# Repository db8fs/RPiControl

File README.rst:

##########
RPiControl
##########

***************************
RaspberryPi 3 Interface
***************************

Hardware
==============

Prozessor
^^^^^^^^^

Der RaspberryPi3 ist ein Ein-Platinen-Computer auf der Grundlage der ARM-Prozessorarchitektur, welche durch die Firma Broadcom lizensiert und im SoC (https://www.raspberrypi.org/wp-content/uploads/2012/02/BCM2835-ARM-Peripherals.pdf) implementiert wurde. Es handelt sich dabei um eine **Quad-Core-SMP**-Architektur mit einem Basistakt von **1.2Ghz** und einer Adressbreite von **64-Bit**. 

GPU
^^^
Der BCM2835-Prozessor ist als System-On-Chip konzipiert und stellt einen Grafikprozessor auf der Grundlage der Broadcom-VideoCoreIV-IP (http://elinux.org/Raspberry_Pi_VideoCore_APIs) bereit. Diese ist in der Lage, Full-HD-Videos abzuspielen und stellt auch OpenGL ES 2.0 bzw. OpenVG für Anwendungen bereit.

Speicher
^^^^^^^^
Wie für fast jegliche Art von Computersystem ist auch für den RaspberryPi3 eine **Speicherhierarchie** definiert. Der schnelle, aber flüchtige Arbeitsspeicher (**RAM**) des RaspberryPi ist mit 900Mhz getaktet (LPDDR2) und steht in einer Kapazität von **1GB** bereit. Das langsame, aber persistente Halten von Daten wird durch eine externe SD-Karte realisiert. 

Netzwerk
^^^^^^^^

Ein wesentlicher Unterschied neben der erhöhten Performance gegenüber dem RaspberryPi2 ist eine neu hinzugekommene Wireless-Funktionalität. So ist der RPi3 bereits im Auslieferungszustand in der Lage, **Bluetooth-LowEnergy** und WLAN-Verbindungen (IEEE 802.11n) herzustellen. Diese Funktionalität wird über den Chipsatz BCM43143 (http://www.cypress.com/file/298756/download) realisiert. Zusätzlich steht wie in den Vorgängermodellen des RPi eine RJ45-Schnittstelle bereit, über die 100MBit-Ethernetverbindungen hergestellt werden können. 

Peripherie
^^^^^^^^^^

Zusätzliche Komponenten des RaspberryPi3 sind die erweiterte Anzahl von USB-Schnittstellen (4x USB 2.0) gegenüber den 2xUSB1.1 vom ursprünglichen Board aus dem Jahre 2012), welche über das Bauteil SMSC LAN9514 (http://ww1.microchip.com/downloads/en/DeviceDoc/9514.pdf) realisiert wird (dieses implementiert gleichzeitig auch den Ethernet-Stack). 
Daneben ist für den RPi3 auch eine **CSI-Kameraschnittstelle** für serielle Datenübertragung von HD-Kameramodulen vorgesehen, mit der entsprechende Kameramodule hochauflösend an den BCM-Prozessor angebunden werden können. 

Zur Darstellung der Benutzeroberfläche dient eine **HDMI-** und eine **DSI-Displayschnittstelle**, über die mittels Differenzsignalen hochfrequent und störungsfrei Daten zu Displays übertragen werden können (**LVDS**). Dies entspricht im Wesentlichen dem Verhalten der HDMI-Schnittstelle, welche zum Anschluss externer Monitore bereitsteht und deren LVDS-Signale durch die oben genannte VideoCore-GPU generiert werden. 

Zur Ausgabe akustischer Signale (Soundkarte) steht ein kombinierter A/V-Adapter zur Verfügung, der durch eine 3.5mm Klinkenstecker eine Stereoausgabe ermöglicht. Zusätzlich wird über einen dritten Kanal ein Composite-Videosignal (PAL/NTSC) bereitgestellt, was zur Videoausgabe auf nicht-HDMI-kompatibler Hardware verwendet werden kann. 

Erweiterungen
^^^^^^^^^^^^^
Für das hier dokumentierte Projekt ist allerdings eine andere Eigenschaft des RaspberryPi entscheidend: der RaspberryPi 3 besitzt nämlich eine 40-polige Steckerleiste zur Anbindung
externer Peripherie. Darüber können universell benutzbare Ein-/Ausgabe-Pins (GPIO=General Purpose I/O) mit LVTTL Pegeln (**3.3V**) geschaltet bzw. hochohmig gelesen werden. Manche
dieser GPIO Pins besitzen eine Doppelbelegung, die bei Konfiguration der richtigen Register des BroadCom-SoCs die Zweitfunktionalität freischaltet. Dies betrifft z.B. Platinenbusse wie **SPI** oder **I²C**, die Ansteuerung von RS232-/ oder RS485-Treibern (**UART**), aber auch die Generierung von externen Signalformen mittels Hardware-unterstützter Pulsweitenmodulation (**PWM**).
Maximal belastbar sind die GPIO-Ausgabekanäle mit **50mA**, was zum direkten Schalten von LEDs ausreicht, für größere Lasten aber Bipolar- bzw. Feldeffekttransistoren benötigt.

Betriebssystem
^^^^^^^^^^^^^^

Der RaspberryPi kann mit verschiedenen Betriebssystemen betrieben werden. Unter anderem stehen verschiedene Linux-Distributionen wie Raspbian (http://www.raspbian.org) oder das für MediaCenter optimierte (http://www.openelec.tv) zur Verfügung. Auch eine Verwendung mit Microsoft-Plattformen ist möglich, so kann etwa auch Windows10-IoT (https://developer.microsoft.com/de-de/windows/iot) für den RaspberryPi3 verwendet werden.

Programmierung
^^^^^^^^^^^^^^

Zur Programmierung eigener Anwendungen ist für Linux-Betriebssysteme die Programmiersprache **Python** (http://www.python.org) das Mittel der Wahl. Sie stellt eine sehr einfache und für Einsteiger leicht zu erlernende Syntax bereit und kann durch **PyQt** (https://riverbankcomputing.com/software/pyqt/intro) leicht grafische Anwendungen erzeugen. Zur Ansteuerung der GPIOs kann die Softwarekomponente **WiringPi** (http://raspberrypiguide.de/howtos/raspberry-pi-gpio-how-to/) genutzt werden. Neben Python stehen auch Compiler für Programmiersprachen wie C/C++, Java oder ADA (http://www.adacore.com/press/adacore-introduces-gnat-gpl-2015-for-the-raspberry-pi-2) bereit. 

Für die Verwendung von Windows 10 IoT muss statt dessen das VisualStudio 2015 (https://developer.microsoft.com/en-us/windows/iot/docs/setuppcrpi) verwendet werden. Damit wird eine Programmierung mit **C#** und dem **.NET Framework** möglich.

GPIO-Extender
^^^^^^^^^^^^^

Hauptkomponente des Projekts ist der integrierte Schaltkreis MCP23017 (http://cdn-reichelt.de/documents/datenblatt/A200/DS_MCP23017.pdf), der als GPIO-Extender fungiert und über den I²C-Bus vom RaspberryPi aus gesteuert werden kann.

Die wesentliche Aufgabe des Bausteins ist die Behebung der Limitierung von I/O-Ports. Der RaspberryPi kann als I²C-Master theoretisch bis zu 127 Slaves adressieren, die Einschränkung soll hier bei maximal 8 Teilnehmern liegen.&lt;p&gt; Der MCP23017 unterstützt zwei Kanäle mit je einer Breite von 8-Bit. Durch Konfiguration eines Datenrichtungsregisters können deren Pins zwischen Input- und Output umgeschaltet werden.

Expansion-Header
^^^^^^^^^^^^^^^^
Die Expansion-Header entsprechen Stiftleisten zur Erweiterung der Funktionalität. So können für ein bestimmte Einsatzzweck erstellte Lochraster- bzw. Platinenaufbauten mit dem Board verwendet werden, solange sie den gleichen Footprint verwenden und die elektrischen Gegebenheiten passend antizipieren.

RJ-45-Steckverbinder
^^^^^^^^^^^^^^^^^^^^^
Zur Verbindung von Busteilnehmern kommen RJ-45-Steckverbinder zum Einsatz, die in der Netzwerktechnik weit verbreitet sind und daher leicht verfügbar bzw. erweiterbar sind. Das betrifft hauptsächlich die einfache und wartungsfreie Montage von Slave-Modulen im Gesamtsystem des Aufbaus. 

**Keine Kompatibilität zu Ethernet-Switches/-Hubs**!

Die Belegung  der RJ-45-Buchse ist **proprietär und inkompatibel zu Ethernet**. 

Konkret leisten muss die RJ45-Buchse:

- Masseverbindung
- Reserviert
- I²C-Clock (+3.3V LVTTL)
- I²C-Data (+3.3V LVTTL)
- +12V DC-Versorgungsspannung
- Reset (Low-Active, +3.3V LVTTL)
- Reserviert
- Reserviert

Somit wird sichergestellt, dass selbst bei Verklemmung des I²C-Busses, ein durch den I²C-Master gesteuertes Reset ausgelöst werden kann. Die restlichen Aufgaben sind Datentransport und Bereitstellung einer gemeinsamen Spannungsquelle für alle Slaves. Die handelsüblichen Cat5-Kabel bieten für dieses kleine I²C-Bussystem auch den Vorteil einer recht hohen Abschirmung gegenüber HF-Einströmungen, da die Adern paarweise geschirmt sind (Twisted-Pair). Damit sollte eine für PWM ausreichend hohe Taktung des I²C-Busses auch über mal 2-3m
hin gewährleistet sein.

I²C-Bus
^^^^^^^
Zur Kommunikation zwischen RaspberryPi und den angeschlossenen Verbrauchern dient der von Philips entwickelte I²C-Bus, der ähnlich wie der SPI-Bus zur Kommunikation zwischen IC auf und zwischen Leiterplatten dient (**I²C=Inter-Integrated-Circuits**). Aus diesem Design folgen ein paar ernsthafte Limitierungen:

- Der I²C-Bus ist **nicht differentiell**, d.h. es wird **nicht** wie etwa bei CAN- oder RS485 mit zwei Datenpotentialen (D+, D-) gearbeitet, deren Differenzspannung vom Empfänger gebildet wird.
- I²C ist somit anfällig für Gleichtaktstörungen (z.B. Zündfunken), hat aufgrund der niedrigen (LV)TTL-Pegel eine begrenzte Reichweite und benötigt ähnlich wie die RS232 immer eine gemeinsame Masse als Bezugspotential.
- I²C ist ein **getakteter Bus**
- I²C ist ein Master-Slave-Bussystem 
- Anzahl Teilnehmer ist auf 127 begrenzt
- Datenbreite für Register ist im Durchschnitt bei 16-Bit (implementierungabhängig)
- Terminierung erforderlich
- Datenraten von bis zu 5Mbit/s möglich
- serieller Bus (MSB-first Übertragung)

Diese Master-Slave-Busarchitektur ermöglicht es dem Master, zyklisch Werte vom Bus abzufragen
(**Polling**). Manche IC-Implementierungen ermöglichen zusätzlich die Verwendung von externen Interrupt-Pins, welche OnChange-Ereignisse signalisieren können. Aufgrund der dadurch resultierenden Verdrahtungskomplexität bietet sich das allerdings nur in speziellen Anwendungsfällen an, wo z.B. ein preiswerter und leistungsbegrenzter 8-Bit-Mikrocontroller (möglicherweise mit Optimierung auf maximale Batterielaufzeit) aufgrund eigener Resourcenrestriktionen und anderen integrierten Funktionen nicht ständig auf den I²C-Bus pollen kann.

Aus der Perspektive des RaspberryPi als I²C-Master bietet sich I²C sehr an, da mit den **i2c-tools** und dem Linux-Kernel-Modul **i2c-bcm2708** eine sehr leistungsstarke und komfortable Schnittstelle zur Arbeit mit I²C bereit steht. Die sehr gute Linux-Unterstützung für I²C rührt u.a. historisch auch daher, dass viele Temperatur-Sensoren auf PC-Mainboards über dieses Protokoll adressiert wurden (Stichwort **lm-sensors**).

Die I²C-Slaves als Teilnehmer müssen mit **eindeutigen Adressen** kodiert sein. Zu diesem Zweck dienen beim MCP23017 die Pins A[0..2], wodurch sich 2³=8 Teilnehmer unterscheiden lassen. Die Slave-Adressierung wird durch den montierten DIP-Schalter durchgeführt.

Versorgung
^^^^^^^^^^
Die Spannungsversorgung ist einheitlich auf +12V DC sichergestellt. Dies zum Einen dem Leistungsteil geschuldet, dessen Verbraucher diese Spannung erfordern, zum Anderen bietet sich dieser Spannungslevel aufgrund der Versorgung durch Kfz-Netzteile etc. an. 
Eine wichtige Rolle für die Versorgungsspannung spielt der I²C-Bus, der zur Kommunikation zwischen dem RaspberryPi und den Busteilnehmern dient. I²C funktioniert im Gegensatz zu CAN-
Bus oder anderen Feldbussystemen wie RS-485 **nicht differenziell**. Das bedeutet in der Konsequenz, dass sowohl **eine gemeinsame Masse**, als auch **ein gemeinsames Versorgungpotential** notwendig ist.

Der Broadcom-ARM-Prozessor des RaspberryPi verwendet sowohl für GPIOs, als auch für SPI und I²C-Bus ein LVTTL-Pegel, d.h. +3.3V, welche sowohl für den I²C-Takt, als auch
für die I²C-Datenleitung gelten.

Somit ergibt sich in der Konsequenz, dass als kleinster gemeinsamer Nenner zwischen RaspberryPi und GPIO-Extender beide auf LVTTL betrieben werden sollten.

Für diese Zwecke wird ein Low-Drop-Spannungsregler von Texas Instruments vom Typ **LM1117** (http://www.ti.com/lit/ds/symlink/lm1117.pdf) eingesetzt.

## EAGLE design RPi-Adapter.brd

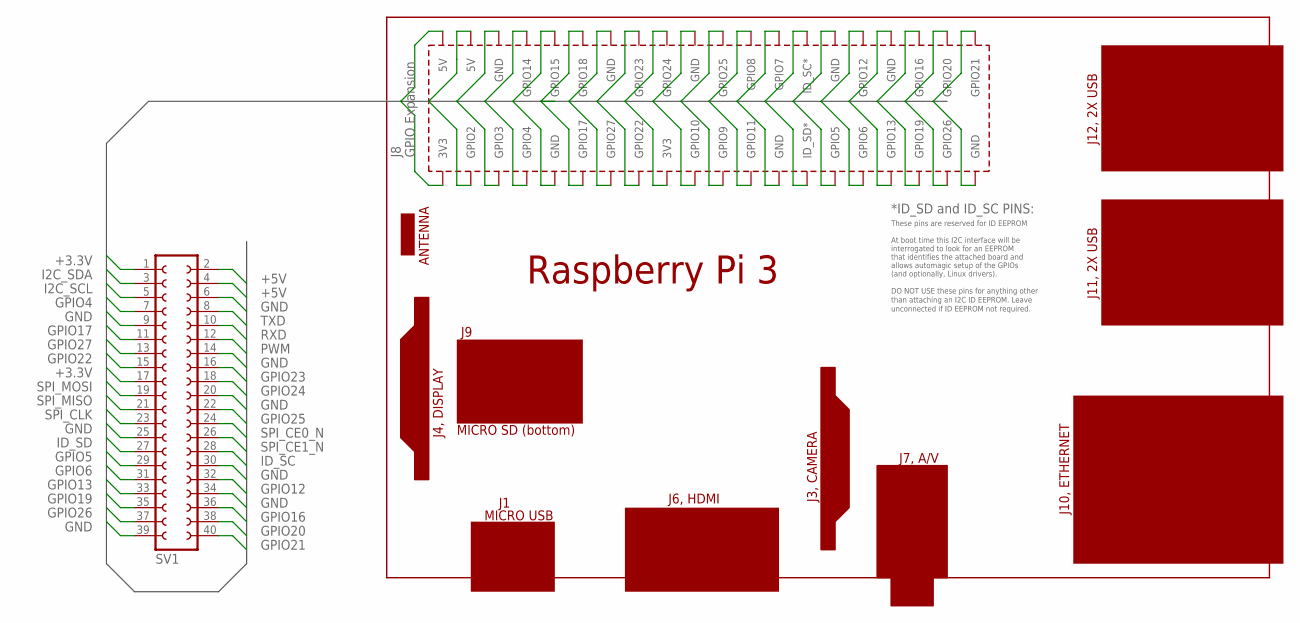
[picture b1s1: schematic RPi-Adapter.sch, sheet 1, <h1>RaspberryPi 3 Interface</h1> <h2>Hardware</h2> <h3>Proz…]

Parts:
SV1: FE20-2

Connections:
+3.3V: SV1.1, SV1.17; also elsewhere on the board
+5V: SV1.2, SV1.4; also elsewhere on the board
GND: SV1.6, SV1.9, SV1.14, SV1.20, SV1.25, SV1.30, SV1.34, SV1.39; also elsewhere on the board
GPIO4: SV1.7; also elsewhere on the board
GPIO5: SV1.29
GPIO6: SV1.31
GPIO12: SV1.32
GPIO13: SV1.33
GPIO16: SV1.36
GPIO17: SV1.11
GPIO19: SV1.35
GPIO20: SV1.38
GPIO21: SV1.40
GPIO22: SV1.15
GPIO23: SV1.16
GPIO24: SV1.18
GPIO25: SV1.22
GPIO26: SV1.37
GPIO27: SV1.13
I2C_SCL: SV1.5; also elsewhere on the board
I2C_SDA: SV1.3; also elsewhere on the board
ID_SC: SV1.28
ID_SD: SV1.27
PWM: SV1.12; also elsewhere on the board
RXD: SV1.10; also elsewhere on the board
SPI_CE0_N: SV1.24; also elsewhere on the board
SPI_CE1_N: SV1.26; also elsewhere on the board
SPI_CLK: SV1.23; also elsewhere on the board
SPI_MISO: SV1.21; also elsewhere on the board
SPI_MOSI: SV1.19; also elsewhere on the board
TXD: SV1.8; also elsewhere on the board

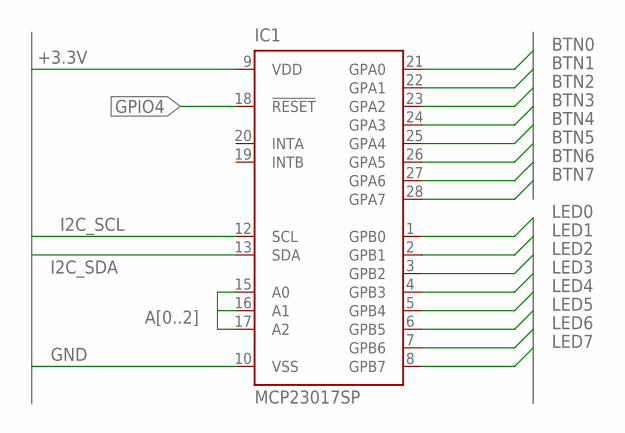
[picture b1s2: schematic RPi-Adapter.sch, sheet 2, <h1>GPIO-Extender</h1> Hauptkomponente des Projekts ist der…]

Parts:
IC1: MCP23017SP; DIL28-3

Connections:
+3.3V: IC1.9 (VDD); also elsewhere on the board
A0: IC1.15 (A0); also elsewhere on the board
A1: IC1.16 (A1); also elsewhere on the board
A2: IC1.17 (A2); also elsewhere on the board
BTN0: IC1.21 (GPA0); also elsewhere on the board
BTN1: IC1.22 (GPA1); also elsewhere on the board
BTN2: IC1.23 (GPA2); also elsewhere on the board
BTN3: IC1.24 (GPA3); also elsewhere on the board
BTN4: IC1.25 (GPA4); also elsewhere on the board
BTN5: IC1.26 (GPA5); also elsewhere on the board
BTN6: IC1.27 (GPA6); also elsewhere on the board
BTN7: IC1.28 (GPA7); also elsewhere on the board
GND: IC1.10 (VSS); also elsewhere on the board
GPIO4: IC1.18 (!RESET); also elsewhere on the board
I2C_SCL: IC1.12 (SCL); also elsewhere on the board
I2C_SDA: IC1.13 (SDA); also elsewhere on the board
LED0: IC1.1 (GPB0); also elsewhere on the board
LED1: IC1.2 (GPB1); also elsewhere on the board
LED2: IC1.3 (GPB2); also elsewhere on the board
LED3: IC1.4 (GPB3); also elsewhere on the board
LED4: IC1.5 (GPB4); also elsewhere on the board
LED5: IC1.6 (GPB5); also elsewhere on the board
LED6: IC1.7 (GPB6); also elsewhere on the board
LED7: IC1.8 (GPB7); also elsewhere on the board

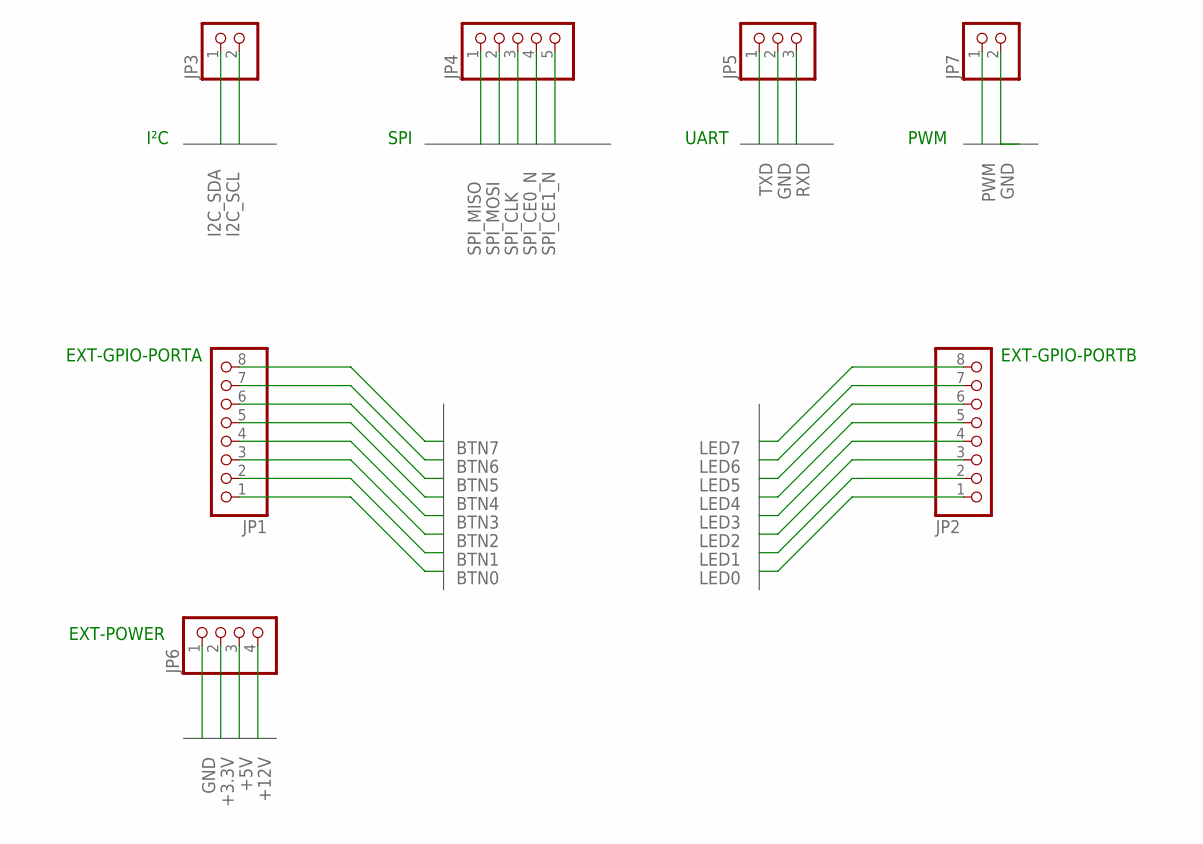
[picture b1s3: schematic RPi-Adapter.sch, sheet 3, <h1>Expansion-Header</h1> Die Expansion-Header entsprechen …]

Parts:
JP1, JP2: PINHD-1X8; 1X08
JP3, JP7: PINHD-1X2; 1X02
JP4: PINHD-1X5; 1X05
JP5: PINHD-1X3; 1X03
JP6: PINHD-1X4; 1X04

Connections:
+3.3V: JP6.2; also elsewhere on the board
+5V: JP6.3; also elsewhere on the board
+12V: JP6.4; also elsewhere on the board
BTN0: JP1.1; also elsewhere on the board
BTN1: JP1.2; also elsewhere on the board
BTN2: JP1.3; also elsewhere on the board
BTN3: JP1.4; also elsewhere on the board
BTN4: JP1.5; also elsewhere on the board
BTN5: JP1.6; also elsewhere on the board
BTN6: JP1.7; also elsewhere on the board
BTN7: JP1.8; also elsewhere on the board
GND: JP5.2, JP6.1, JP7.2; also elsewhere on the board
I2C_SCL: JP3.2; also elsewhere on the board
I2C_SDA: JP3.1; also elsewhere on the board
LED0: JP2.1; also elsewhere on the board
LED1: JP2.2; also elsewhere on the board
LED2: JP2.3; also elsewhere on the board
LED3: JP2.4; also elsewhere on the board
LED4: JP2.5; also elsewhere on the board
LED5: JP2.6; also elsewhere on the board
LED6: JP2.7; also elsewhere on the board
LED7: JP2.8; also elsewhere on the board
PWM: JP7.1; also elsewhere on the board
RXD: JP5.3; also elsewhere on the board
SPI_CE0_N: JP4.4; also elsewhere on the board
SPI_CE1_N: JP4.5; also elsewhere on the board
SPI_CLK: JP4.3; also elsewhere on the board
SPI_MISO: JP4.1; also elsewhere on the board
SPI_MOSI: JP4.2; also elsewhere on the board
TXD: JP5.1; also elsewhere on the board

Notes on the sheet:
EXT-GPIO-PORTA
EXT-GPIO-PORTB
I²C
SPI
UART
EXT-POWER
PWM

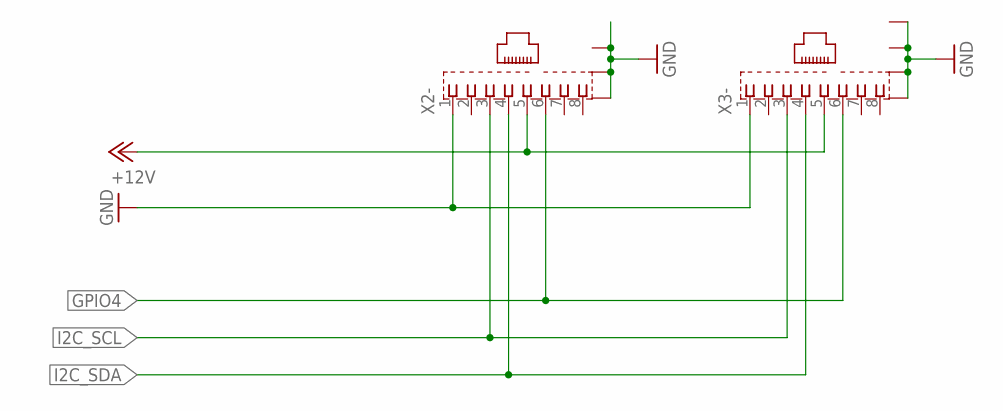
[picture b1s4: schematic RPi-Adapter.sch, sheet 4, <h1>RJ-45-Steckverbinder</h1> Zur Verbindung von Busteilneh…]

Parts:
X2, X3: RJ45

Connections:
+12V: X2.5, X3.5; also elsewhere on the board
GND: X2.1, X2.G1 (1), X2.G2 (1), X2.G3 (1), X3.1, X3.G1 (1), X3.G2 (1), X3.G3 (1), X3.G4 (1); also elsewhere on the board
GPIO4: X2.6, X3.6; also elsewhere on the board
I2C_SCL: X2.3, X3.3; also elsewhere on the board
I2C_SDA: X2.4, X3.4; also elsewhere on the board

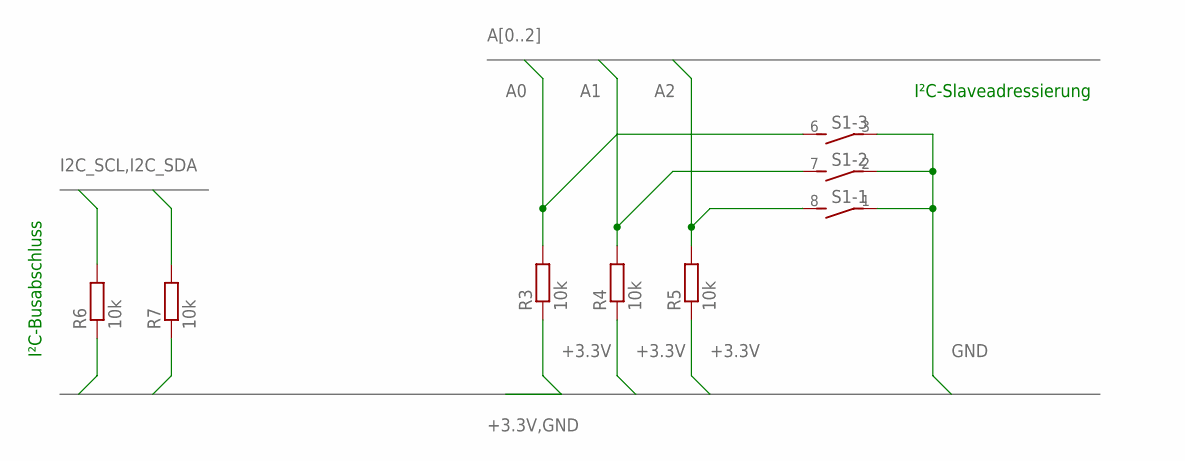
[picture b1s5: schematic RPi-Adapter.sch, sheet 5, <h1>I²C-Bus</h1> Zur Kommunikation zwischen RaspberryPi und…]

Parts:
R3, R4, R5, R6, R7: 10k; R0805
S1: DIP04S

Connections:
+3.3V: R3.1, R4.1, R5.1, R6.1, R7.1; also elsewhere on the board
A0: R3.2, S1.6 (2); also elsewhere on the board
A1: R4.2, S1.7 (2); also elsewhere on the board
A2: R5.2, S1.8 (2); also elsewhere on the board
GND: S1.1, S1.2 (1), S1.3 (1); also elsewhere on the board
I2C_SCL: R6.2; also elsewhere on the board
I2C_SDA: R7.2; also elsewhere on the board

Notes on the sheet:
I²C-Busabschluss
I²C-Slaveadressierung

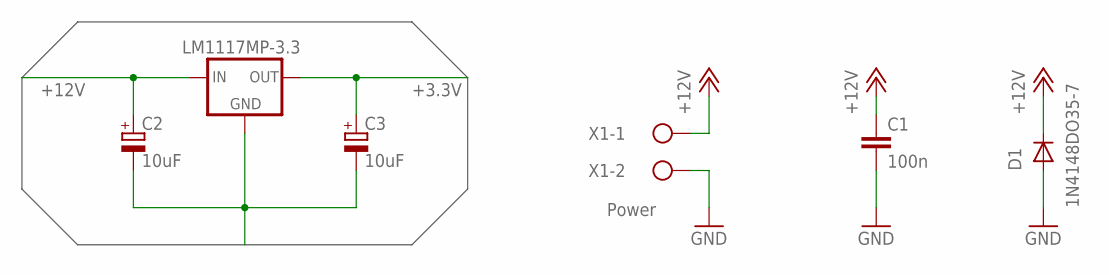
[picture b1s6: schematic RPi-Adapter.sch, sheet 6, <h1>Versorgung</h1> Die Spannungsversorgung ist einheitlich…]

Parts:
C1: 100n; C0805
C2, C3: 10uF; 153CLV-0405
D1: 1N4148DO35-7; DO35-7
IC2: LM1117MP-3.3; SOT223
X1: Power; AK500/2

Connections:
+3.3V: C3.+, IC2.2 (OUT), IC2.4 (OUT); also elsewhere on the board
+12V: C1.1, C2.+, D1.C, IC2.3 (IN), X1.1; also elsewhere on the board
GND: C1.2, C2.-, C3.-, D1.A, IC2.1 (GND), X1.2; also elsewhere on the board

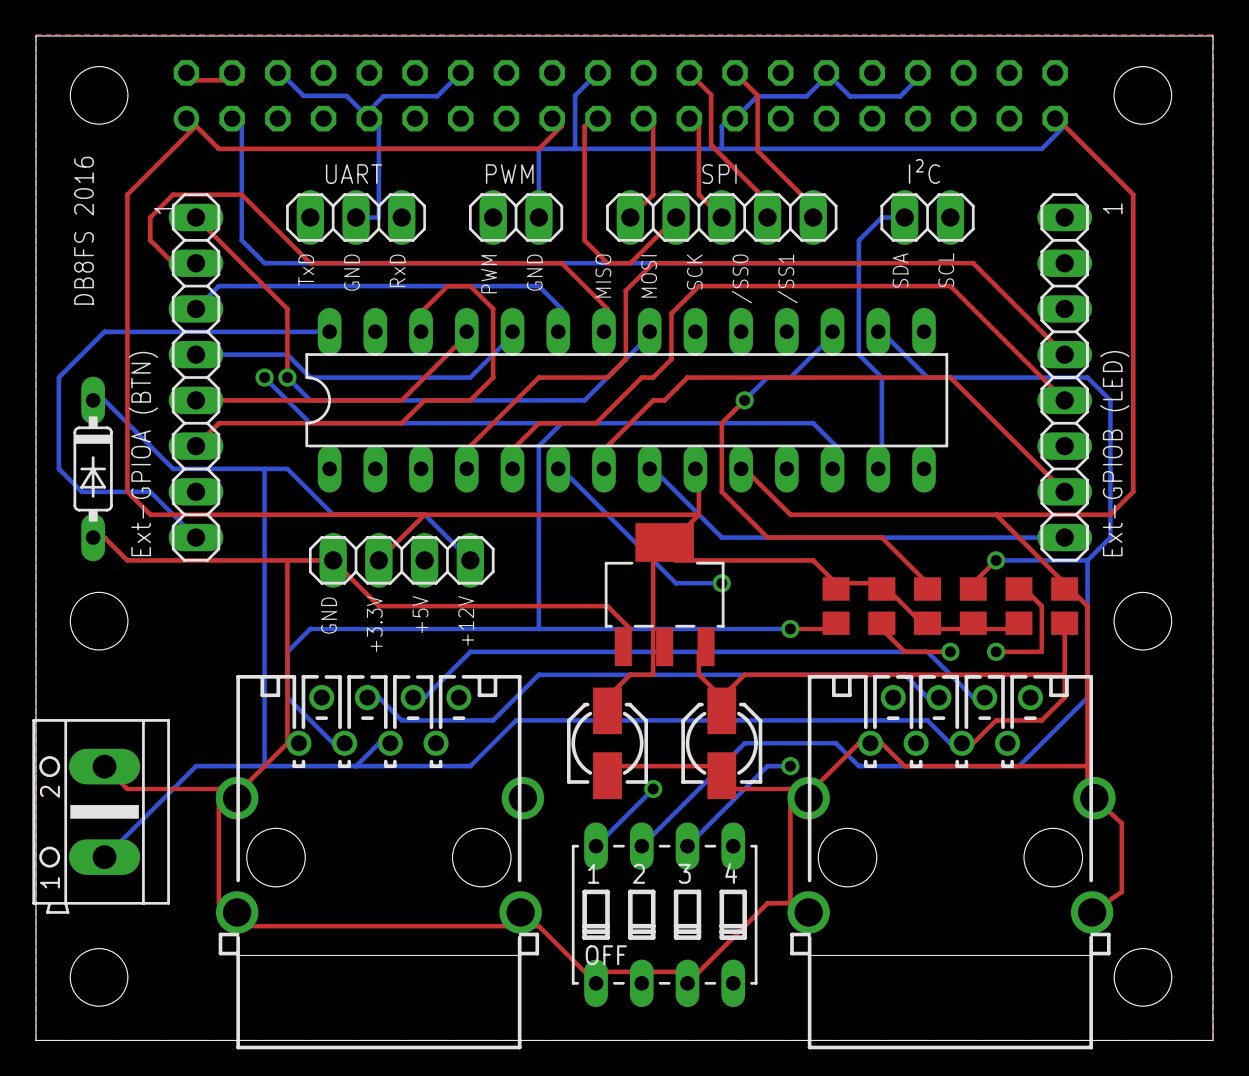
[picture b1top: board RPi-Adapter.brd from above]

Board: 4 copper layers, 65.4 x 55.8 mm, 23 parts (1 on the bottom side), 34 nets.

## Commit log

2016-12-03 First manufactured prototype board
2016-12-03 Extract Eagle schematics documentation into README.rst
2016-12-23 Documentation: update README.rst
